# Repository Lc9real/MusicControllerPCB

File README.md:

"# MusicControllerPCB" 
"# MusicControllerPCB" 
"# MusicControllerPCB"

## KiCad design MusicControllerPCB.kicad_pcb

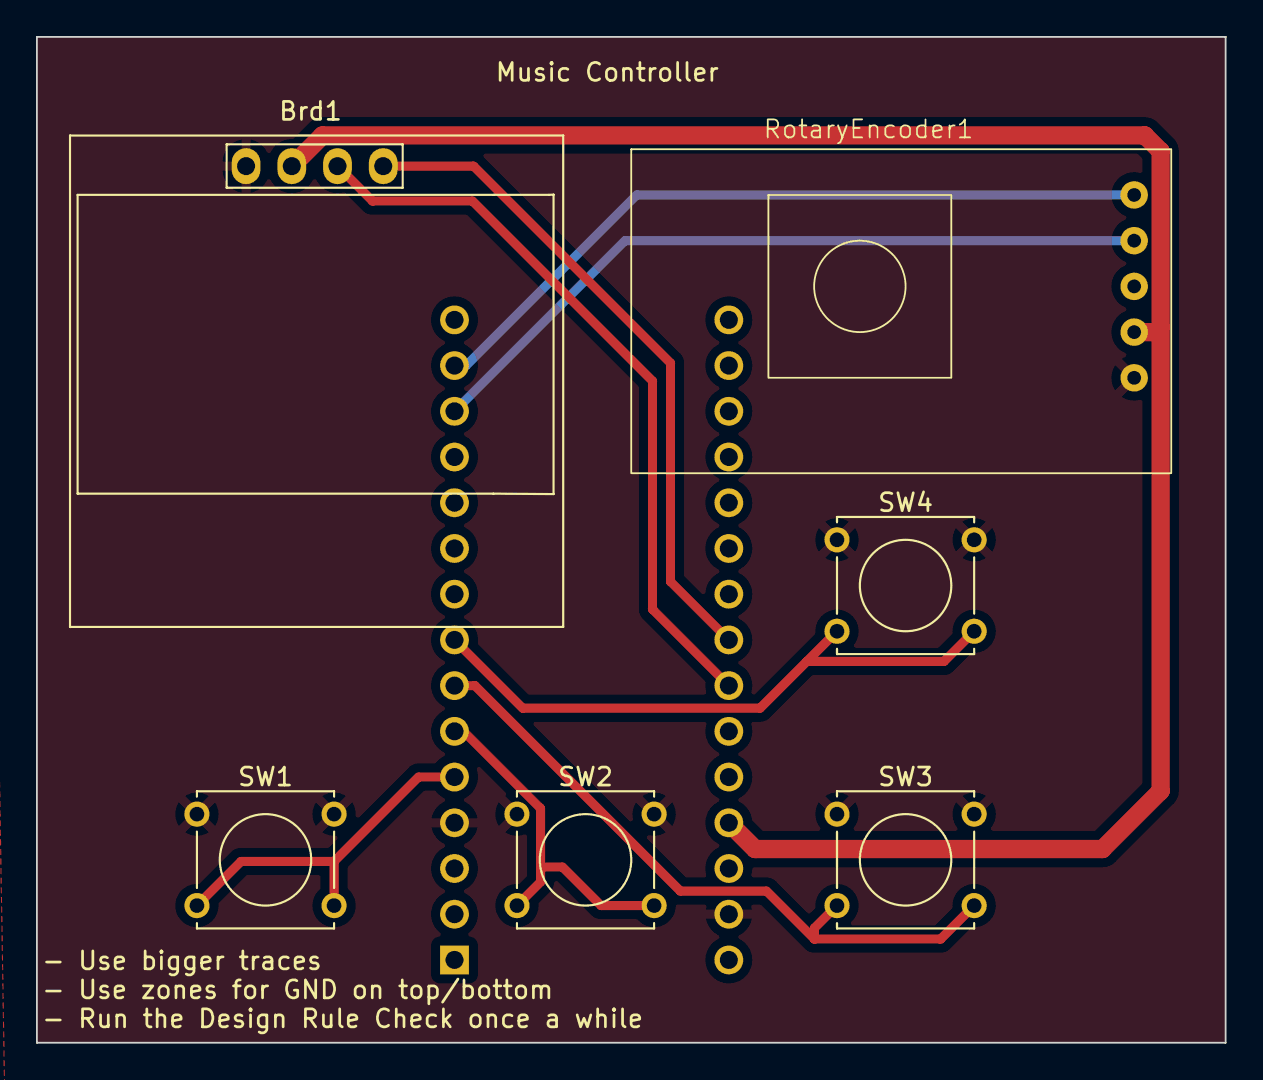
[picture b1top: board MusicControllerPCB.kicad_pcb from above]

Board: 2 copper layers, 66.0 x 55.9 mm, 7 parts (1 on the bottom side), 10 nets.

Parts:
A101: Arduino_Nano_v3.x; Arduino_Nano
Brd1: SSD1306; 128x64OLED
RotaryEncoder1: RotaryEncoder
SW1, SW2, SW3, SW4: SW_Push; SW_Tactile_Straight_KSL0Axx1LFTR

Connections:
+5V: A101.27 (+5V), Brd1.2 (VCC), RotaryEncoder1.4 (+)
/Rot_{CLK}: A101.14 (D11), RotaryEncoder1.1 (CLK)
/Rot_{DT}: A101.13 (D10), RotaryEncoder1.2 (DT)
GND: A101.4 (GND), A101.29 (GND), Brd1.1 (GND), RotaryEncoder1.5 (GND), SW1.1, SW2.1, SW3.1, SW4.1
unnamed: A101.23 (A4), Brd1.4 (SDA)
unnamed: A101.24 (A5), Brd1.3 (SCL)
unnamed: A101.5 (D2), SW1.2
unnamed: A101.6 (D3), SW2.2
unnamed: A101.7 (D4), SW3.2
unnamed: A101.8 (D5), SW4.2

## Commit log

2023-12-01 Create ja
2023-12-01 Some cleanup
2023-12-01 Some files were missing
2023-12-01 Added export
2023-12-01 Made the symbols local to the project
2023-12-01 Nano USB now faces North
